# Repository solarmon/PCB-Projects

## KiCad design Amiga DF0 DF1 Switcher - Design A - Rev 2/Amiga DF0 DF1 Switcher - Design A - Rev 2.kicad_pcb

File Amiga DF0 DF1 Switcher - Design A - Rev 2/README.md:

# Amiga DF0 DF1 Switcher - Design A - Rev 2

This is an Amiga A500/A500+ DF0/DF1 Switcher. It has been designed to sit directly on the floppy drive data port, and for the floppy power to connect to it. It then splits them out so that two internal drives can be connected.

It can work in two modes:

* **DF0 / DF1 Switcher** - this switches DF0 and DF1 between the two internal drives. 
* **DF0 Selector** - this switches only DF0 between the two internal drive - so only one drive will be DF0.

This switching / selection is done using a DPDT On-On switch connected to the **SW1** header pins.

The **JP1** jumper connects or disconnects SEL1. This effectively changes the mode without messing about with the DPDT switch:

* **JP1 Bridged** - DF0/DF1 Switcher mode
* **JP1 Unbridged** - DFO Selector mode

Top:

Bottom:

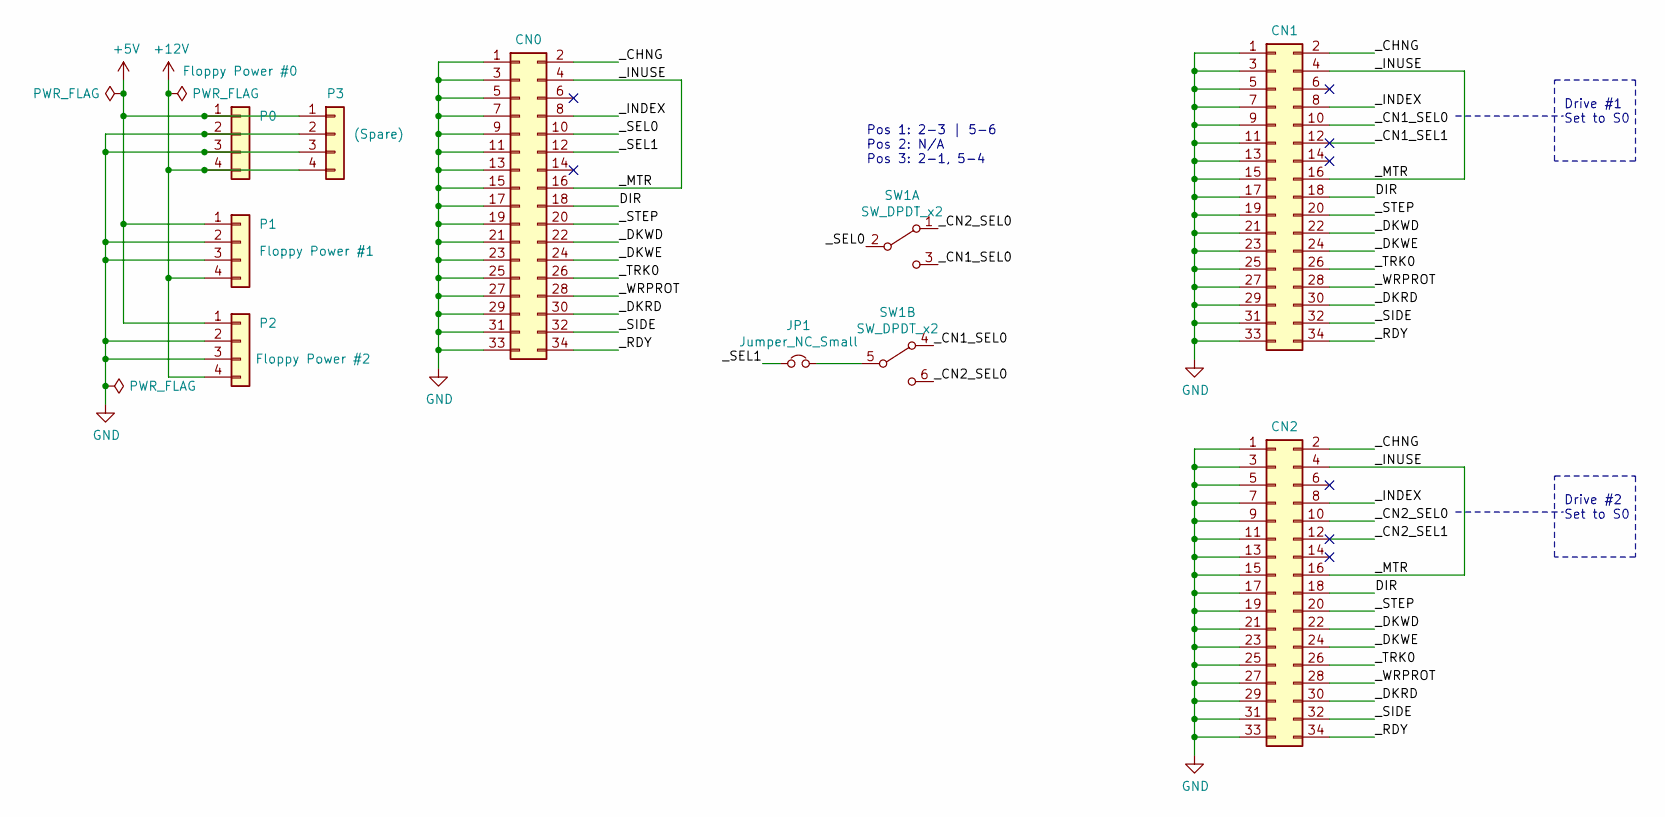
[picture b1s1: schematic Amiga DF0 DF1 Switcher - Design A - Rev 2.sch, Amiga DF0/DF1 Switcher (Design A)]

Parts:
CN0: Conn_02x17_Odd_Even; PinSocket_2x17_P2.54mm_Vertical
CN1, CN2: Conn_02x17_Odd_Even; PinHeader_2x17_P2.54mm_Vertical
JP1: Jumper_NC_Small; PinHeader_1x02_P2.54mm_Vertical
P0: Floppy Power #0; PinHeader_1x04_P2.54mm_Vertical
P1: Floppy Power #1; PinHeader_1x04_P2.54mm_Vertical
P2: Floppy Power #2; PinHeader_1x04_P2.54mm_Vertical
P3: (Spare); PinHeader_1x04_P2.54mm_Vertical
SW1: SW_DPDT_x2; PinHeader_2x03_P2.54mm_Vertical_DPDT

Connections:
+5V: P0.1, P1.1, P2.1, P3.1
+12V: P0.4, P1.4, P2.4, P3.4
/DIR: CN0.18, CN1.18, CN2.18
/_CHNG: CN0.2, CN1.2, CN2.2
/_CN1_SEL0: CN1.10, SW1.3 (C), SW1.4 (A)
/_CN1_SEL1: CN1.12
/_CN2_SEL0: CN2.10, SW1.1 (A), SW1.6 (C)
/_CN2_SEL1: CN2.12
/_DKRD: CN0.30, CN1.30, CN2.30
/_DKWD: CN0.22, CN1.22, CN2.22
/_DKWE: CN0.24, CN1.24, CN2.24
/_INDEX: CN0.8, CN1.8, CN2.8
/_INUSE: CN0.4, CN0.16, CN1.4, CN1.16, CN2.4, CN2.16
/_RDY: CN0.34, CN1.34, CN2.34
/_SEL0: CN0.10, SW1.2 (B)
/_SEL1: CN0.12, JP1.1
/_SIDE: CN0.32, CN1.32, CN2.32
/_STEP: CN0.20, CN1.20, CN2.20
/_TRK0: CN0.26, CN1.26, CN2.26
/_WRPROT: CN0.28, CN1.28, CN2.28
GND: CN0.1, CN0.3, CN0.5, CN0.7, CN0.9, CN0.11, CN0.13, CN0.15, CN0.17, CN0.19, CN0.21, CN0.23, CN0.25, CN0.27, CN0.29, CN0.31, CN0.33, CN1.1, CN1.3, CN1.5, CN1.7, CN1.9, CN1.11, CN1.13, CN1.15, CN1.17, CN1.19, CN1.21, CN1.23, CN1.25, CN1.27, CN1.29, CN1.31, CN1.33, CN2.1, CN2.3, CN2.5, CN2.7, CN2.9, CN2.11, CN2.13, CN2.15, CN2.17, CN2.19, CN2.21, CN2.23, CN2.25, CN2.27, CN2.29, CN2.31, CN2.33, P0.2, P0.3, P1.2, P1.3, P2.2, P2.3, P3.2, P3.3
unnamed: JP1.2, SW1.5 (B)

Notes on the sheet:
Drive #1 Set to S0
Drive #2 Set to S0
Pos 1: 2-3 | 5-6 Pos 2: N/A Pos 3: 2-1, 5-4

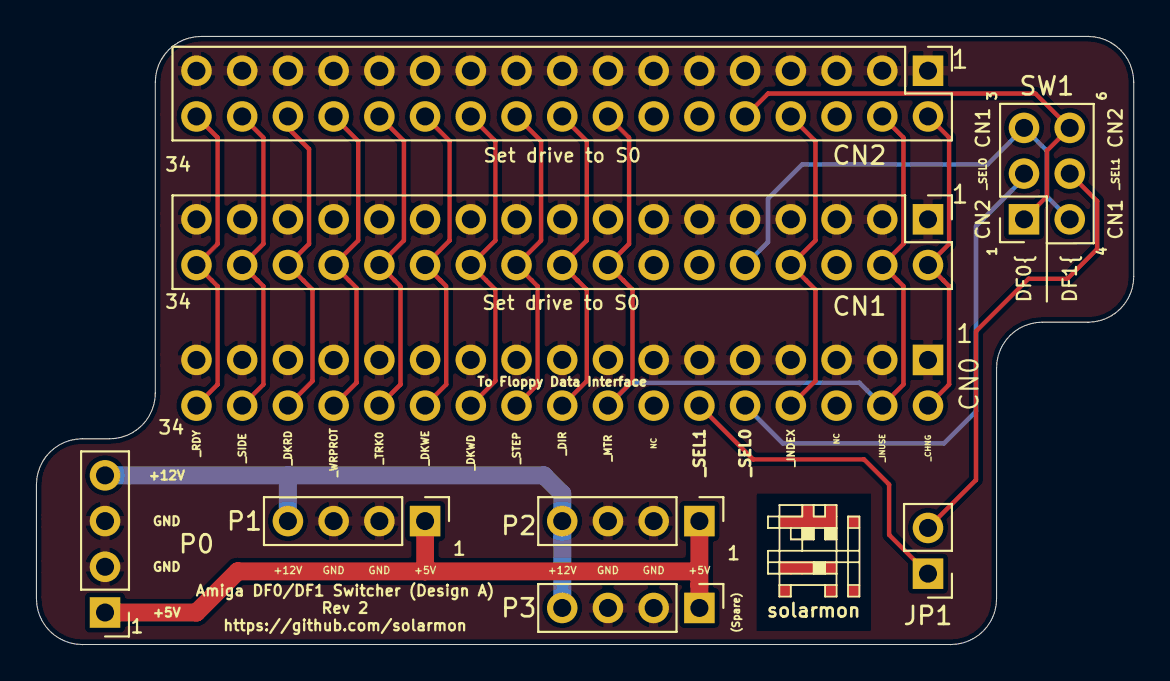
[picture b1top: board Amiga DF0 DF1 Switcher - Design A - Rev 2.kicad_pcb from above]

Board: 2 copper layers, 61.0 x 33.8 mm, 10 parts (1 on the bottom side), 20 nets.

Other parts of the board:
solarmon: solarmon-logo-25mils

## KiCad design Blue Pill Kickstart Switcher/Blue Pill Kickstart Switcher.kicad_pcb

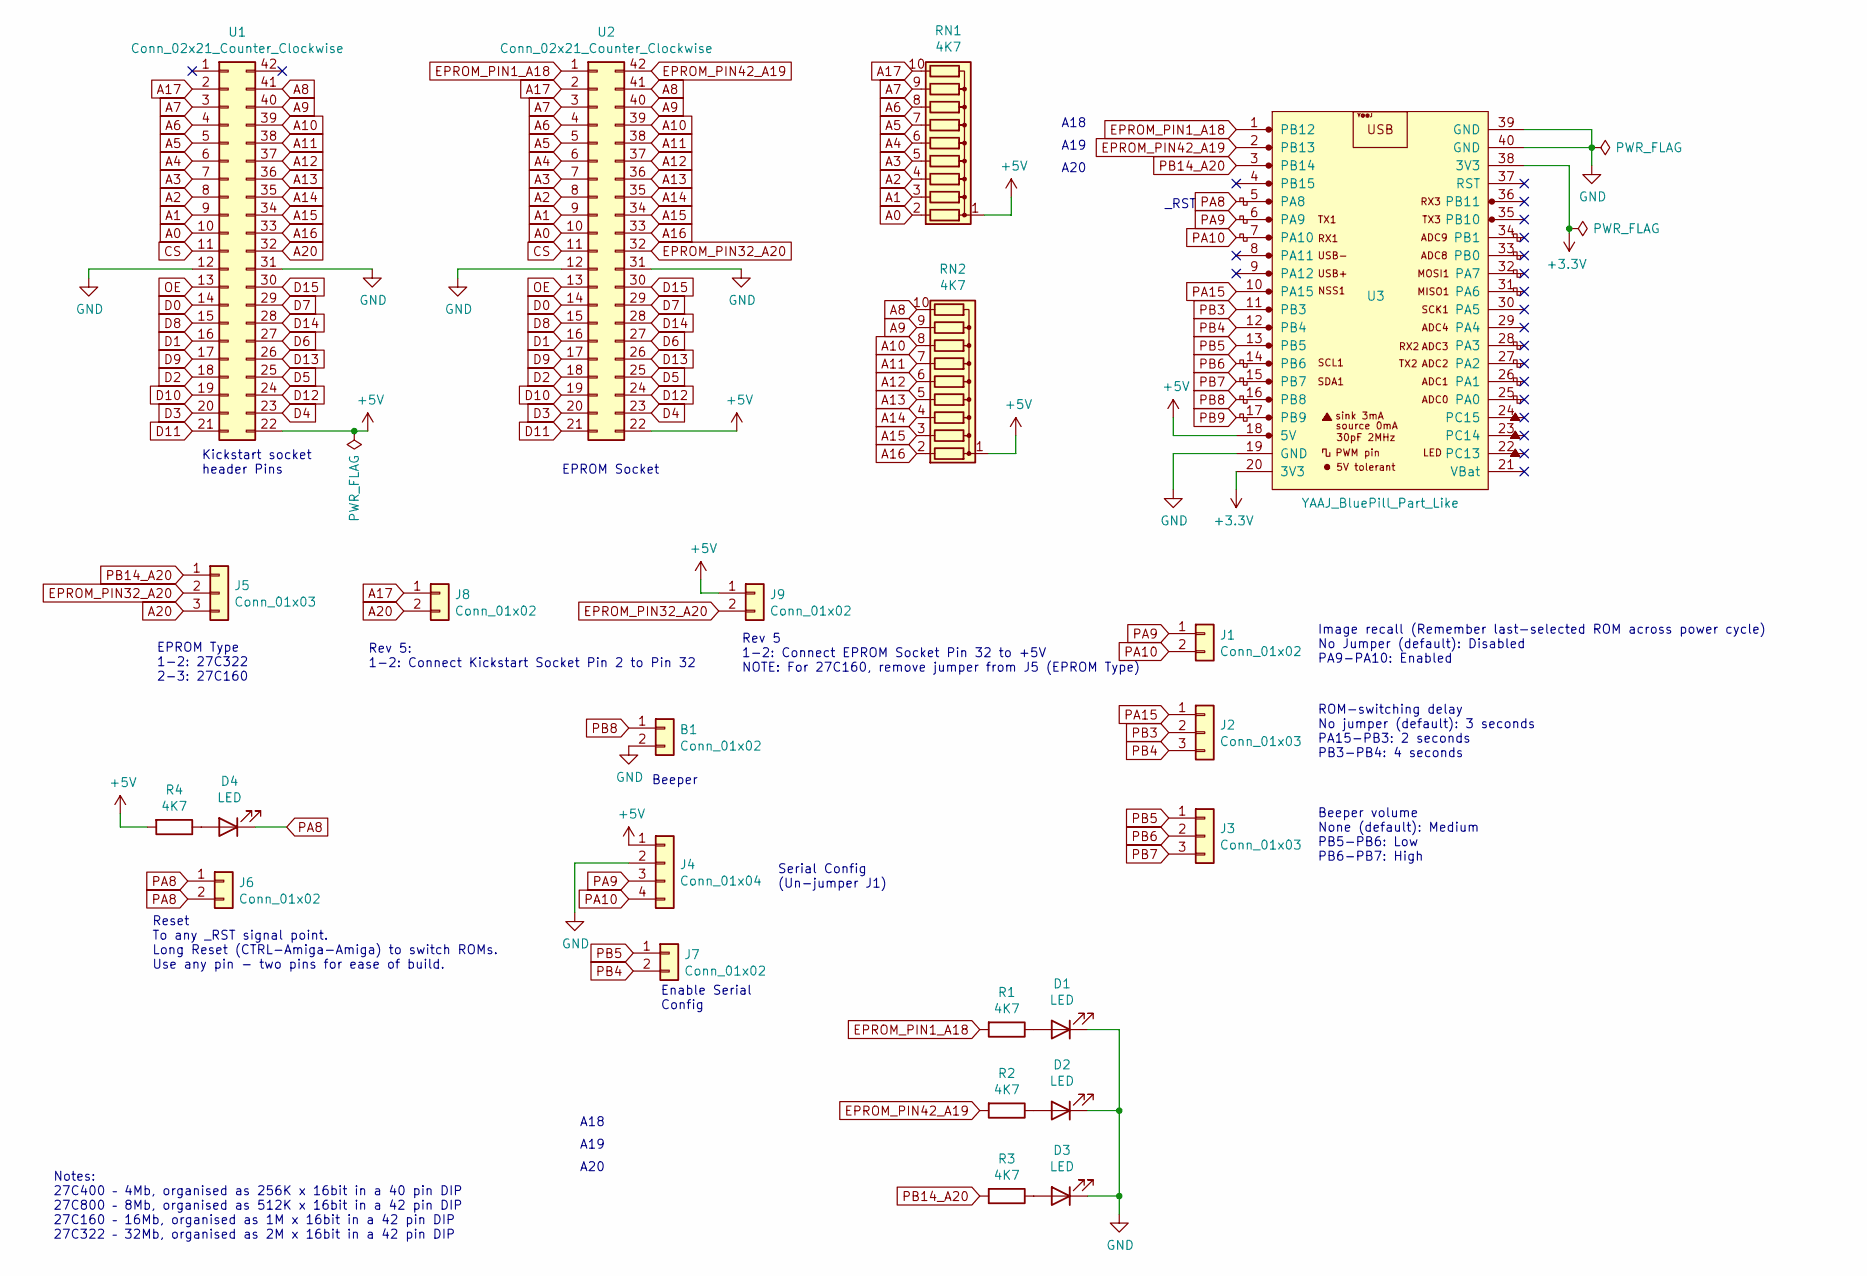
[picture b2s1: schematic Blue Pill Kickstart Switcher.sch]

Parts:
B1: Conn_01x02; Buzzer
D1, D2, D3, D4: LED; LED_0805_2012Metric_Pad1.15x1.40mm_HandSolder
J1, J6, J7, J8, J9: Conn_01x02; PinHeader_1x02_P2.54mm_Horizontal
J2, J3, J5: Conn_01x03; PinHeader_1x03_P2.54mm_Horizontal
J4: Conn_01x04; PinHeader_1x04_P2.54mm_Horizontal
R1, R2, R3, R4: 4K7; R_0805_2012Metric_Pad1.20x1.40mm_HandSolder
RN1, RN2: 4K7; R_Array_SIP10
U1: Conn_02x21_Counter_Clockwise; DIP-42_W15.24mm_Pin_Header_Bottom
U2: Conn_02x21_Counter_Clockwise; DIP-42_W15.24mm_Socket
U3: YAAJ_BluePill_Part_Like; YAAJ_BluePill_1

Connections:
+3V3: U3.20 (3V3), U3.38 (3V3)
+5V: J4.1, J9.1, R4.2, RN1.1 (common), RN2.1 (common), U1.22, U2.22, U3.18 (5V)
A0: RN1.2 (R1), U1.10, U2.10
A1: RN1.3 (R2), U1.9, U2.9
A2: RN1.4 (R3), U1.8, U2.8
A3: RN1.5 (R4), U1.7, U2.7
A4: RN1.6 (R5), U1.6, U2.6
A5: RN1.7 (R6), U1.5, U2.5
A6: RN1.8 (R7), U1.4, U2.4
A7: RN1.9 (R8), U1.3, U2.3
A8: RN2.10 (R9), U1.41, U2.41
A9: RN2.9 (R8), U1.40, U2.40
A10: RN2.8 (R7), U1.39, U2.39
A11: RN2.7 (R6), U1.38, U2.38
A12: RN2.6 (R5), U1.37, U2.37
A13: RN2.5 (R4), U1.36, U2.36
A14: RN2.4 (R3), U1.35, U2.35
A15: RN2.3 (R2), U1.34, U2.34
A16: RN2.2 (R1), U1.33, U2.33
A17: J8.1, RN1.10 (R9), U1.2, U2.2
A20: J5.3, J8.2, U1.32
CS: U1.11, U2.11
D0: U1.14, U2.14
D1: U1.16, U2.16
D2: U1.18, U2.18
D3: U1.20, U2.20
D4: U1.23, U2.23
D5: U1.25, U2.25
D6: U1.27, U2.27
D7: U1.29, U2.29
D8: U1.15, U2.15
D9: U1.17, U2.17
D10: U1.19, U2.19
D11: U1.21, U2.21
D12: U1.24, U2.24
D13: U1.26, U2.26
D14: U1.28, U2.28
D15: U1.30, U2.30
EPROM_PIN1_A18: R1.2, U2.1, U3.1 (PB12)
EPROM_PIN32_A20: J5.2, J9.2, U2.32
EPROM_PIN42_A19: R2.2, U2.42, U3.2 (PB13)
GND: B1.2, D1.1 (K), D2.1 (K), D3.1 (K), J4.2, U1.12, U1.31, U2.12, U2.31, U3.19 (GND), U3.39 (GND), U3.40 (GND)
unnamed: D1.2 (A), R1.1
unnamed: D2.2 (A), R2.1
unnamed: D3.2 (A), R3.1
unnamed: D4.2 (A), R4.1
OE: U1.13, U2.13
PA8: D4.1 (K), J6.1, J6.2, U3.5 (PA8)
PA9: J1.1, J4.3, U3.6 (PA9)
PA10: J1.2, J4.4, U3.7 (PA10)
PA15: J2.1, U3.10 (PA15)
PB3: J2.2, U3.11 (PB3)
PB4: J2.3, J7.2, U3.12 (PB4)
PB5: J3.1, J7.1, U3.13 (PB5)
PB6: J3.2, U3.14 (PB6)
PB7: J3.3, U3.15 (PB7)
PB8: B1.1, U3.16 (PB8)
PB9: U3.17 (PB9)
PB14_A20: J5.1, R3.2, U3.3 (PB14)

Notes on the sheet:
Beeper
Beeper volume None (default): Medium PB5-PB6: Low PB6-PB7: High
Image recall (Remember last-selected ROM across power cycle) No Jumper (default): Disabled PA9-PA10: Enabled
ROM-switching delay No jumper (default): 3 seconds PA15-PB3: 2 seconds PB3-PB4: 4 seconds
Serial Config (Un-jumper J1)
Enable Serial Config
Notes: 27C400 – 4Mb, organised as 256K x 16bit in a 40 pin DIP 27C800 – 8Mb, organised as 512K x 16bit in a 42 pin DIP 27C160 – 16Mb, organised as 1M x 16bit in a 42 pin DIP 27C322 – 32Mb, organised as 2M x 16bit in a 42 pin DIP
_RST
EPROM Socket
Kickstart socket header Pins
A18
A19
A20
Reset To any _RST signal point. Long Reset (CTRL-Amiga-Amiga) to switch ROMs. Use any pin - two pins for ease of build.
EPROM Type 1-2: 27C322 2-3: 27C160
Rev 5: 1-2: Connect Kickstart Socket Pin 2 to Pin 32
Rev 5 1-2: Connect EPROM Socket Pin 32 to +5V NOTE: For 27C160, remove jumper from J5 (EPROM Type)

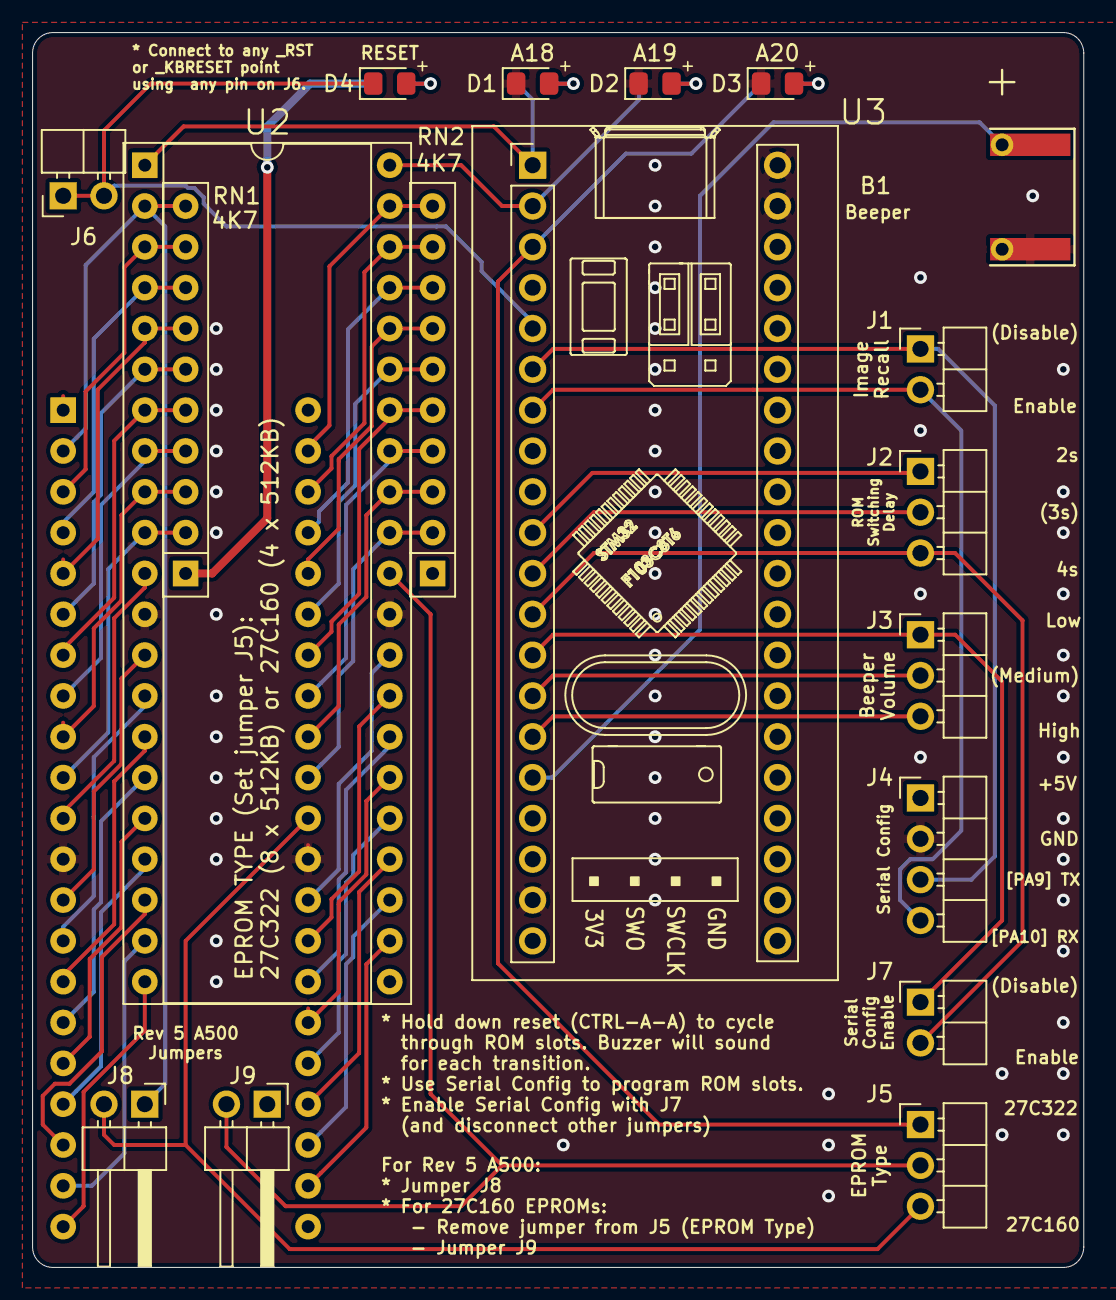
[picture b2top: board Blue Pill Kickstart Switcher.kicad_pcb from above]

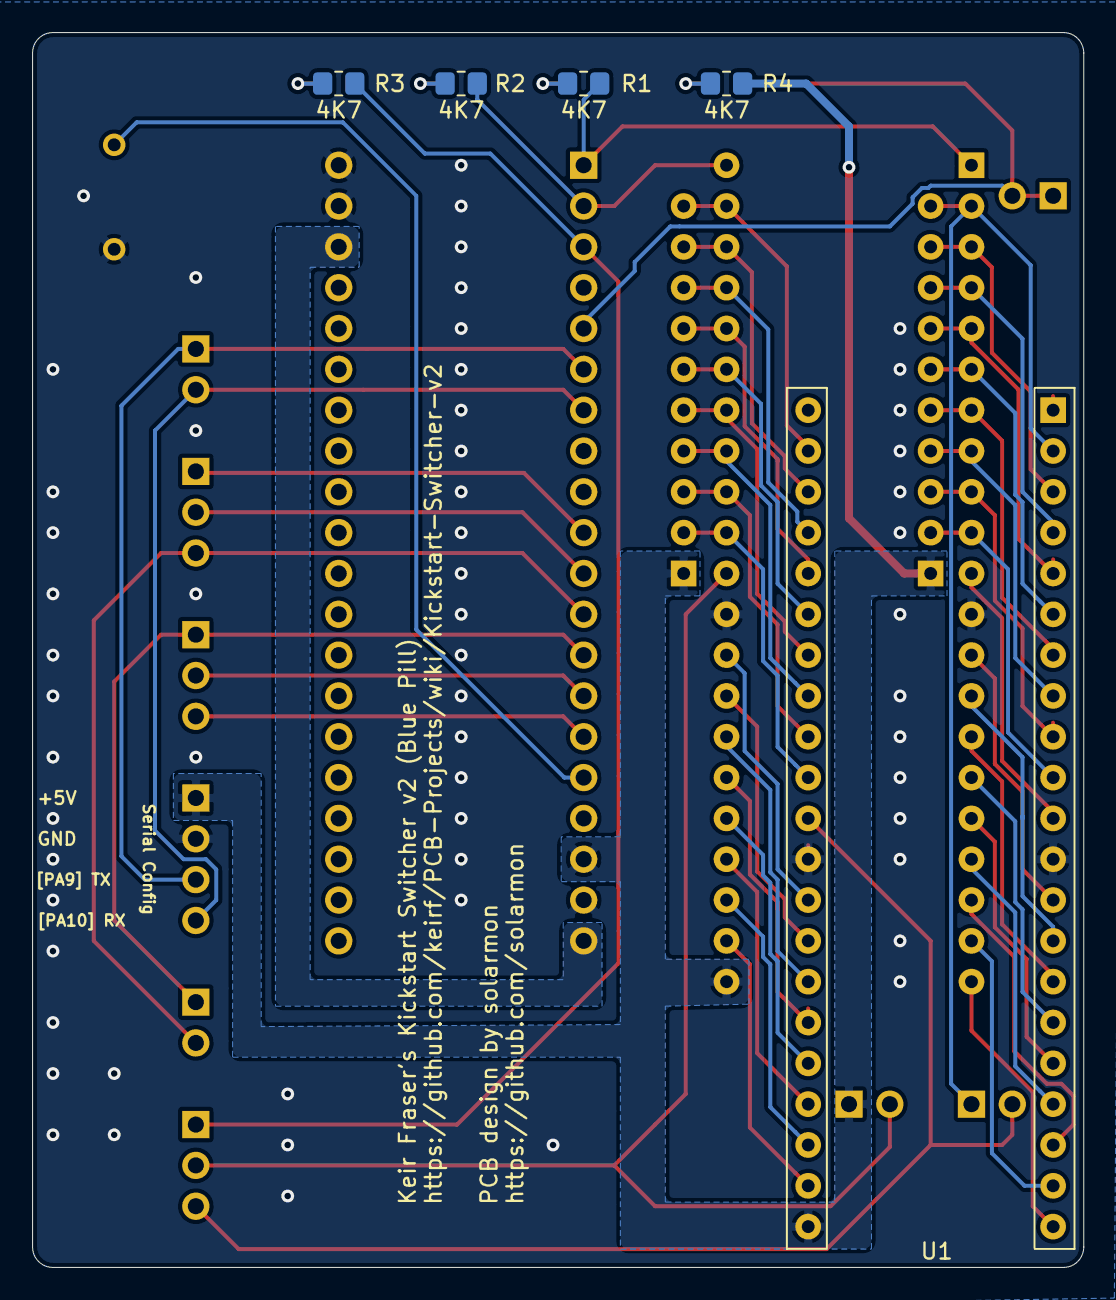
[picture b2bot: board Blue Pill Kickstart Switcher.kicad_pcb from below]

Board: 2 copper layers, 65.4 x 76.8 mm, 23 parts (4 on the bottom side), 58 nets.

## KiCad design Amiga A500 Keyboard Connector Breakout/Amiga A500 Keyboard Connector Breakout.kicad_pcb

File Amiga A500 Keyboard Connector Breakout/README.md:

# Amiga A500 Keyboard Connector Breakout

This is a breakout board for the A500/A500+ keyboard connector to allow access to the signals on it.

The keyboard connector has the following pinouts and signals:

1. _KBCLOCK
2. _KBDATA
3. _KBRESET
4. +5V
5. (KEY)
6. GND
7. STATUS (POWER LED)
8. INUSE (DRIVE LED)

The board provides a female header at the bottom of the board that sits on the keyboard connector on the motherboard, and provides two sets of corresponding header pins - one for the keyboard plug to connect to and the other for as per user requirements.

The board also has an LED for the the _KBRESET, STATUS and INUSE signals to provide a quick indicate of the state of those signals. This also means you don't need a keyboard connected to see the POWER and DRIVE LEDs.

The board also provides some pin headers for the +5V and GND power rails, useful to power additional boards and for diagnostics tools such as a logic probe.

Top of the breakout board:

Bottom of the breakout board:

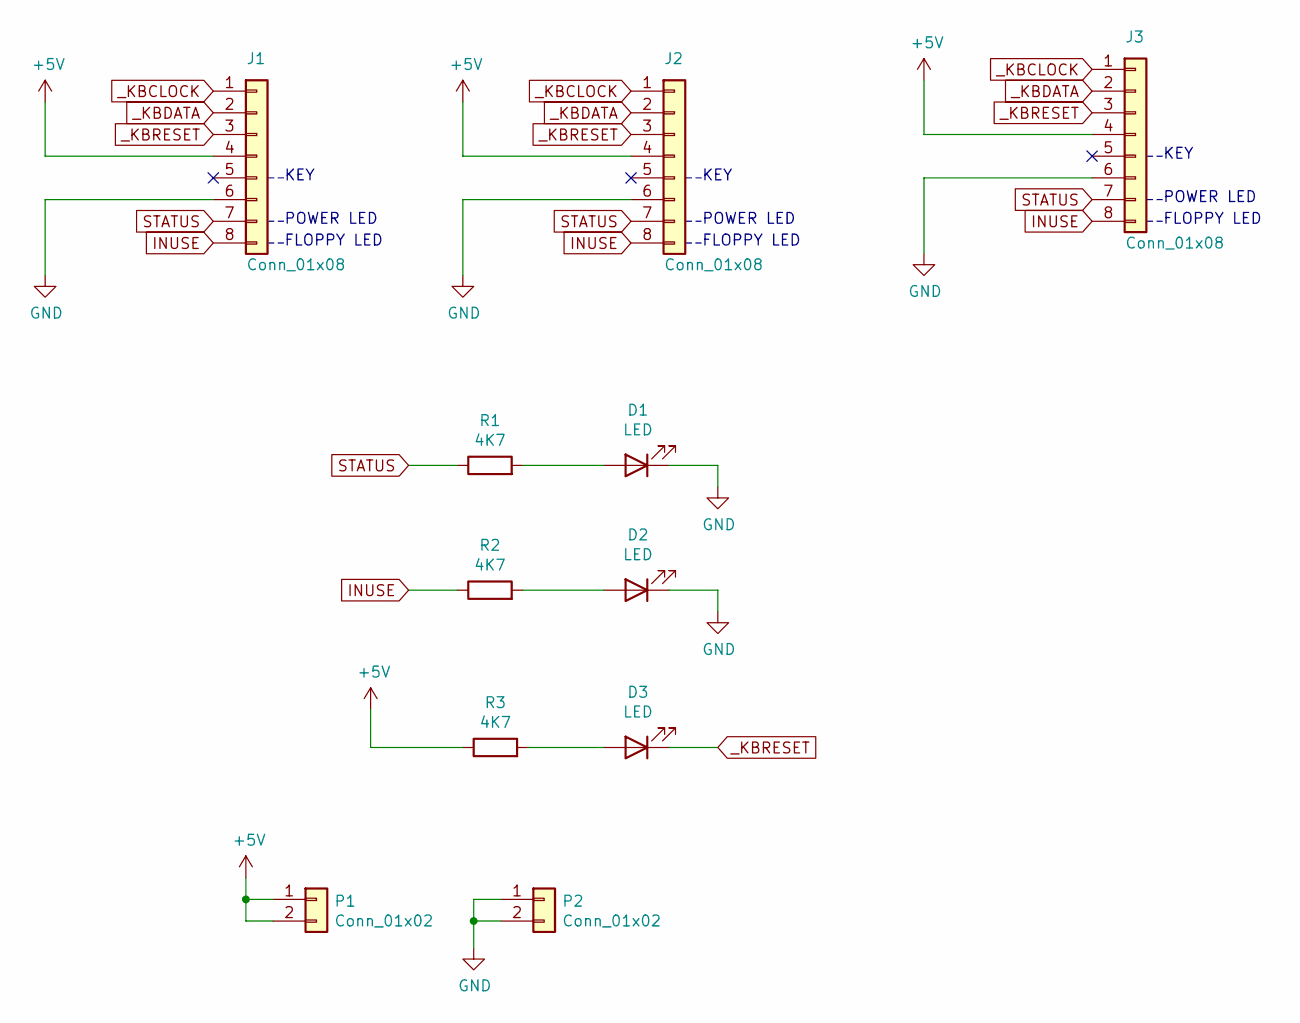
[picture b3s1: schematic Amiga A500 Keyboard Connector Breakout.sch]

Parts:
D1, D2, D3: LED; LED_0805_2012Metric_Pad1.15x1.40mm_HandSolder
J1: Conn_01x08; PinSocket_1x08_P2.54mm_Vertical
J2, J3: Conn_01x08; PinHeader_1x08_P2.54mm_Vertical
P1, P2: Conn_01x02; PinHeader_1x02_P2.54mm_Vertical
R1, R2, R3: 4K7; R_0805_2012Metric_Pad1.20x1.40mm_HandSolder

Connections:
+5V: J1.4, J2.4, J3.4, P1.1, P1.2, R3.1
GND: D1.1 (K), D2.1 (K), J1.6, J2.6, J3.6, P2.1, P2.2
INUSE: J1.8, J2.8, J3.8, R2.1
unnamed: D1.2 (A), R1.2
unnamed: D2.2 (A), R2.2
unnamed: D3.2 (A), R3.2
STATUS: J1.7, J2.7, J3.7, R1.1
_KBCLOCK: J1.1, J2.1, J3.1
_KBDATA: J1.2, J2.2, J3.2
_KBRESET: D3.1 (K), J1.3, J2.3, J3.3

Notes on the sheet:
POWER LED
FLOPPY LED
KEY

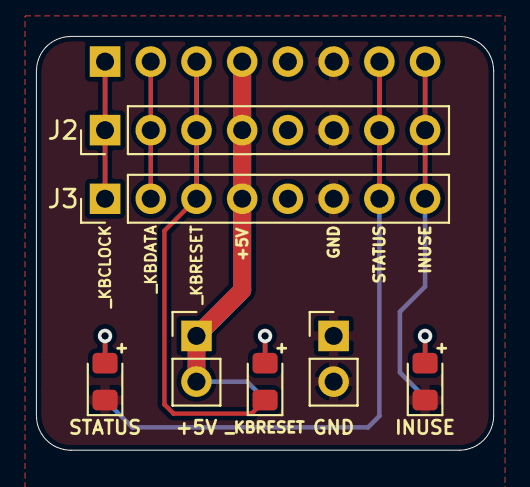
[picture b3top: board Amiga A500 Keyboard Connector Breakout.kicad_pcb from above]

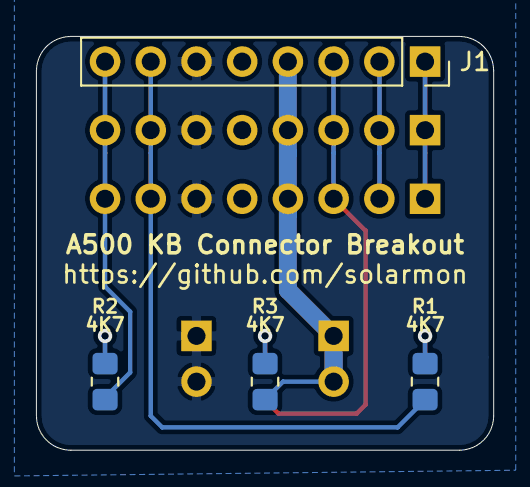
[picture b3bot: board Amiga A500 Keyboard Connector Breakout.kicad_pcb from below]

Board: 2 copper layers, 25.4 x 23.0 mm, 11 parts (4 on the bottom side), 10 nets.

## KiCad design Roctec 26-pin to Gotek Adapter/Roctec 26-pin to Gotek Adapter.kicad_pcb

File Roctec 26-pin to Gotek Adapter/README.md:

# Roctec 26-pin to Gotek Adapter

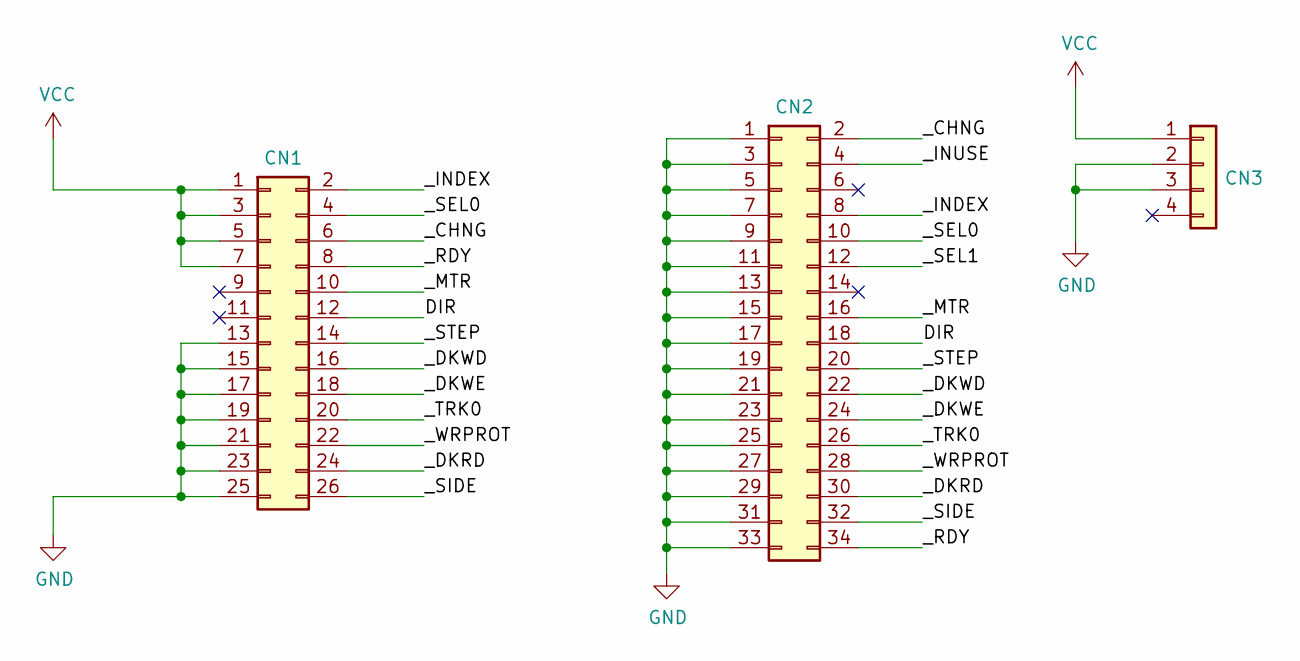
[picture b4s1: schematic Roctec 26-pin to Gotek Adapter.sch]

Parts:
CN1: Conn_02x13_Odd_Even; PinHeader_2x13_P2.54mm_Vertical
CN2: Conn_02x17_Odd_Even; PinSocket_1x17_P2.54mm_Horizontal
CN3: Conn_01x04; PinSocket_1x04_P2.54mm_Horizontal

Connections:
/DIR: CN1.12, CN2.18
/_CHNG: CN1.6, CN2.2
/_DKRD: CN1.24, CN2.30
/_DKWD: CN1.16, CN2.22
/_DKWE: CN1.18, CN2.24
/_INDEX: CN1.2, CN2.8
/_INUSE: CN2.4
/_MTR: CN1.10, CN2.16
/_RDY: CN1.8, CN2.34
/_SEL0: CN1.4, CN2.10
/_SEL1: CN2.12
/_SIDE: CN1.26, CN2.32
/_STEP: CN1.14, CN2.20
/_TRK0: CN1.20, CN2.26
/_WRPROT: CN1.22, CN2.28
GND: CN1.13, CN1.15, CN1.17, CN1.19, CN1.21, CN1.23, CN1.25, CN2.1, CN2.3, CN2.5, CN2.7, CN2.9, CN2.11, CN2.13, CN2.15, CN2.17, CN2.19, CN2.21, CN2.23, CN2.25, CN2.27, CN2.29, CN2.31, CN2.33, CN3.2, CN3.3
VCC: CN1.1, CN1.3, CN1.5, CN1.7, CN3.1

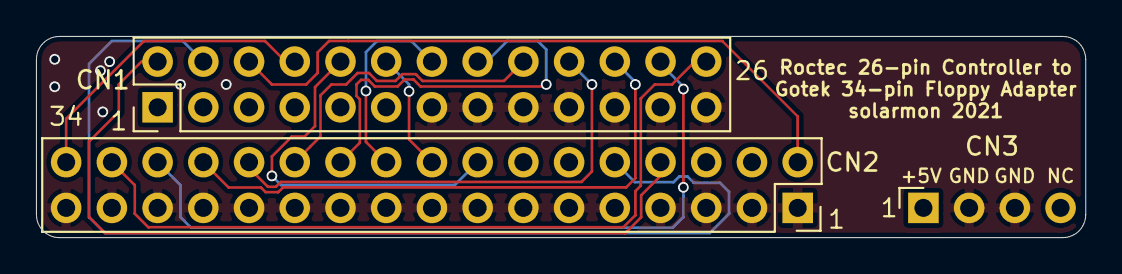
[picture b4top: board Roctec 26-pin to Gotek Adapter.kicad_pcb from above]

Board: 2 copper layers, 58.3 x 11.2 mm, 3 parts (0 on the bottom side), 15 nets.

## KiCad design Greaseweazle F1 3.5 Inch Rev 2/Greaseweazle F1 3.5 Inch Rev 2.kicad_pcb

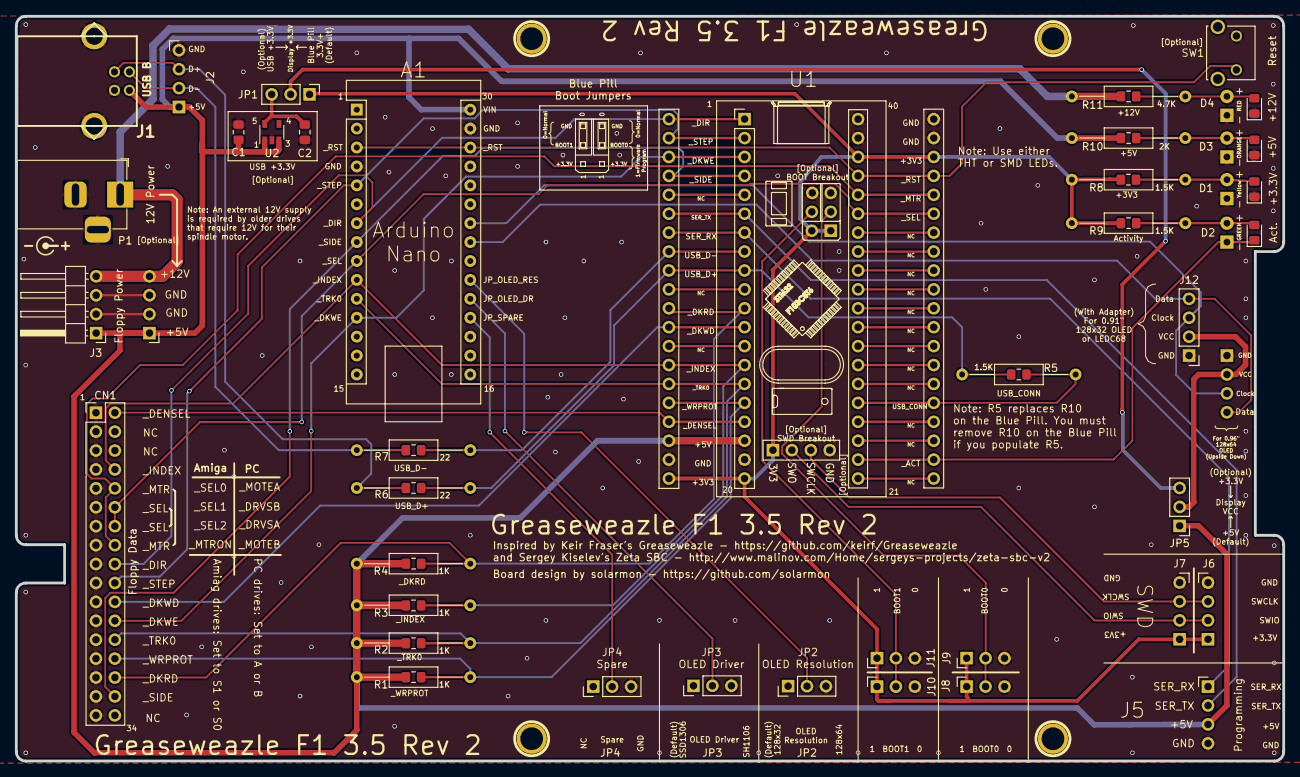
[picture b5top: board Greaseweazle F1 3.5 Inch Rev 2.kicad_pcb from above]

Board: 2 copper layers, 170.2 x 100.0 mm, 67 parts (1 on the bottom side), 56 nets.

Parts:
A1: Arduino_Nano_v3.x; Arduino_Nano
BP1, BP2: Conn_01x20_Male; PinHeader_1x20_P2.54mm_Vertical
C1, C2: 1u; C_0805_2012Metric_Pad1.15x1.40mm_HandSolder
CN1: Floppy Data; PinHeader_2x17_P2.54mm_Vertical
D1: +3V3 LED; LED_0805_2012Metric_Pad1.15x1.40mm_HandSolder
D1#2, D2#2, D3#2, D4: LED_D3.0mm_Horizontal_O1.27mm_Z6.0mm
D2: ACT LED; LED_0805_2012Metric_Pad1.15x1.40mm_HandSolder
D3, D4#2: +5V LED; LED_0805_2012Metric_Pad1.15x1.40mm_HandSolder
Floppy Drive: Floppy_Drive
HEX: Hex_standoff_m3_15mm
HEX#2, HEX#3, HEX#4: Hex_standoff_m3_15mm
HOLE1, HOLE2, HOLE3, HOLE4: CONN_1; HOLE_3MM
J1: USB B; conn_usb_B
J2: USB Header; PinHeader_1x04_P2.54mm_Horizontal
J3: Floppy Power; PinHeader_1x04_P2.54mm_Horizontal
J4: Floppy Power Header; PinHeader_1x04_P2.54mm_Horizontal
J5: Programming Port; PinHeader_1x04_P2.54mm_Horizontal
J6, J7: SWD Port; PinHeader_1x04_P2.54mm_Horizontal
J8, J9, J10, J11: Conn_01x03; PinHeader_1x03_P2.54mm_Horizontal
J12, J13: Display Port; PinHeader_1x04_P2.54mm_Vertical
JP1, JP2, JP3, JP4, JP5: Jumper_3_Bridged12; PinHeader_1x03_P2.54mm_Vertical
P1: 12V Power; BarrelJack_Horizontal
R1, R2, R3, R4: 1K; R_0805_2012Metric_Pad1.15x1.40mm_HandSolder
R1#2, R2#2, R3#2, R4#2, R5#2, R6#2, R7#2, R8#2, R9#2, R10#2, R11: R_Axial_DIN0207_L6.3mm_D2.5mm_P15.24mm_Horizontal
R5, R8, R9: 1.5K; R_0805_2012Metric_Pad1.15x1.40mm_HandSolder
R6, R7: 22; R_0805_2012Metric_Pad1.15x1.40mm_HandSolder
R10: 2K; R_0805_2012Metric_Pad1.15x1.40mm_HandSolder
R11#2: 4.7K; R_0805_2012Metric_Pad1.15x1.40mm_HandSolder
SW1: Reset; PUSH_BUTTON_RIGHT_ANGLE
U1: Blue Pill; YAAJ_BluePill_SWD_1_BootPins
U2: AP2112K-3.3; SOT-23-5

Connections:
+3V3: BP1.20, BP2.18, J6.1, J7.1, J8.1, J9.1, J10.1, J11.1, JP1.1, R8.2, R8#2.2, R9.2, R9#2.2, U1.20, U1.38, U1.41, U1.45, U1.48
+5V: A1.30, BP1.18, C1.1, J1.1, J2.1, J3.1, J4.1, J5.3, JP5.1, R1.1, R1#2.2, R2.1, R2#2.2, R3.1, R3#2.2, R4.1, R4#2.2, R10.2, R10#2.2, U1.18, U2.1, U2.3
+12V: J3.4, J4.4, P1.1, R11.2, R11#2.2
/BOOT0: J8.2, J9.2, U1.46
/BOOT1: J10.2, J11.2, U1.49
/Display_3V3: JP1.2, JP5.3
/Display_Clock: A1.24, J12.3, J13.3
/Display_Data: A1.23, J12.4, J13.4
/Display_VCC: J12.2, J13.2, JP5.2
/JP_OLED_DR: A1.20, JP3.2
/JP_OLED_RES: A1.21, JP2.2
/JP_SPARE: A1.19, JP4.2
/SER_RX: BP1.7, J5.1, U1.7
/SER_TX: BP1.6, J5.2, U1.6
/SWD_SWCLK: J6.3, J7.3, U1.43
/SWD_SWIO: J6.2, J7.2, U1.42
/USB_3V3: C2.1, JP1.3, U2.5
/USB_CONN: BP2.5, R5.2, R5#2.2, U1.25
/USB_D+: BP1.9, R5.1, R5#2.1, R6.2, R6#2.1, U1.9
/USB_D-: BP1.8, R7.2, R7#2.1, U1.8
/_ACT: BP2.2, D2.1, D2#2.1, U1.22
/_DENSEL: BP1.17, CN1.2, U1.17
/_DIR: A1.7, BP1.1, CN1.18, U1.1
/_DKRD: BP1.11, CN1.30, R4.2, R4#2.1, U1.11
/_DKWD: BP1.12, CN1.22, U1.12
/_DKWE: A1.12, BP1.3, CN1.24, U1.3
/_INDEX: A1.10, BP1.14, CN1.8, R3.2, R3#2.1, U1.14
/_MTR: BP2.16, CN1.10, CN1.16, U1.36
/_RST: A1.3, A1.28, BP2.17, SW1.1, U1.37
/_SEL: A1.9, BP2.15, CN1.12, CN1.14, U1.35
/_SIDE: A1.8, BP1.4, CN1.32, U1.4
/_STEP: A1.5, BP1.2, CN1.20, U1.2
/_TRK0: A1.11, BP1.15, CN1.26, R2.2, R2#2.1, U1.15
/_WRPROT: BP1.16, CN1.28, R1.2, R1#2.1, U1.16
GND: A1.4, A1.29, BP1.19, BP2.19, BP2.20, C1.2, C2.2, CN1.1, CN1.3, CN1.5, CN1.7, CN1.9, CN1.11, CN1.13, CN1.15, CN1.17, CN1.19, CN1.21, CN1.23, CN1.25, CN1.27, CN1.29, CN1.31, CN1.33, D1.1, D1#2.1, D3.1, D3#2.1, D4.1, D4#2.1, HOLE1.1, HOLE2.1, HOLE3.1, HOLE4.1, J1.4, J1.5, J2.4, J3.2, J3.3, J4.2, J4.3, J5.4, J6.4, J7.4, J8.3, J9.3, J10.3, J11.3, J12.1, J13.1, JP2.3, JP3.3, JP4.3, P1.2, P1.3, SW1.2, U1.19, U1.39, U1.40, U1.44, U1.47, U1.50, U2.2
unnamed: BP1.5, U1.5
unnamed: BP1.10, U1.10
unnamed: BP1.13, U1.13
unnamed: BP2.1, U1.21
unnamed: BP2.3, U1.23
unnamed: BP2.4, U1.24
unnamed: BP2.6, U1.26
unnamed: BP2.7, U1.27
unnamed: BP2.8, U1.28
unnamed: BP2.9, U1.29
unnamed: BP2.10, U1.30
unnamed: BP2.11, U1.31
unnamed: BP2.12, U1.32
unnamed: BP2.13, U1.33
unnamed: BP2.14, U1.34
unnamed: D1.2, D1#2.2, R8.1, R8#2.1
unnamed: D2.2, D2#2.2, R9.1, R9#2.1
unnamed: D3.2, D3#2.2, R10.1, R10#2.1
unnamed: D4.2, D4#2.2, R11.1, R11#2.1
unnamed: J1.2, J2.2, R7.1, R7#2.2
unnamed: J1.3, J2.3, R6.1, R6#2.2

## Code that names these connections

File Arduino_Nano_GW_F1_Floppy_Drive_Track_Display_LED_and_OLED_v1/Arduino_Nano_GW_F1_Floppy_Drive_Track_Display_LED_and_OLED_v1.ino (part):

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const byte STEP_Pin = 2;   // D2 (D2 and D3 are interrupt capable)

int DIR_Pin = 4;    // D4
int SIDE_Pin = 5;   // D5
int SEL_Pin = 6;   // D6
int INDEX_Pin = 7;  // D7
int TRK0_Pin = 8;   // D8
int DKWE_Pin = 9;   // D9

int JP_SPARE_Pin = 14;      // D14 / A0
int JP_OLED_DR_Pin = 15;    // D15 / A1
int JP_OLED_RES_Pin = 16;   // D16 / A2


// variables to store the drive signal states
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  // Make interrupt for STEP pin, so that falling edge can be detected.
  pinMode(STEP_Pin, INPUT_PULLUP);
  attachInterrupt(digitalPinToInterrupt(STEP_Pin), stepping, FALLING);
  pinMode(INDEX_Pin, INPUT_PULLUP);
  pinMode(SIDE_Pin, INPUT_PULLUP);
  pinMode(TRK0_Pin, INPUT_PULLUP);
  pinMode(SEL_Pin, INPUT_PULLUP);
  pinMode(DKWE_Pin, INPUT_PULLUP);

  //----------------------------

  // Check Jumpers

  pinMode(JP_SPARE_Pin, INPUT_PULLUP);
  pinMode(JP_OLED_RES_Pin, INPUT_PULLUP);
  pinMode(JP_OLED_DR_Pin, INPUT_PULLUP);

  JP_SPARE_State = digitalRead(JP_SPARE_Pin);
  JP_OLED_RES_State = digitalRead(JP_OLED_RES_Pin);
  JP_OLED_DR_State = digitalRead(JP_OLED_DR_Pin);

  Serial.print(F("### JP_SPARE_State: "));
  Serial.print(JP_SPARE_State);
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          // Poll the drive signals
          DIR_State = digitalRead(DIR_Pin);
          STEP_State = digitalRead(STEP_Pin);
          SIDE_State = digitalRead(SIDE_Pin);
          INDEX_State = digitalRead(INDEX_Pin);
          TRK0_State = digitalRead(TRK0_Pin);
          SEL_State = digitalRead(SEL_Pin); // LOW = STEP IN; HIGH = STEP OUT
          DKWE_State = digitalRead(DKWE_Pin);

          if (TRK0_State == 0)
          {
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
          DIR_State = digitalRead(DIR_Pin);
          STEP_State = digitalRead(STEP_Pin);
          SIDE_State = digitalRead(SIDE_Pin);
          INDEX_State = digitalRead(INDEX_Pin);
          TRK0_State = digitalRead(TRK0_Pin);
          SEL_State = digitalRead(SEL_Pin); // LOW = STEP IN; HIGH = STEP OUT
          DKWE_State = digitalRead(DKWE_Pin);
          
          oled_display.clearDisplay (); // clear display

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
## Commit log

2020-11-21 First draft
2020-11-21 Some improvements
    Made bottom side a filled zone for GND and moved floppy power connector to other side for shorter VCC tracks.
2020-11-21 3D view of board
2020-11-22 More improvements
    * Improved GND net points
    * Test points in appropropriate nets
    * Added additional VCC trace
2020-11-22 Added VCC zone
2020-11-22 More improvements
    * Changed _INDEX signal so that it does not go through a test point.
    * Top row of test points on CN1 now have been put in the appropriate nets
2020-11-22 Created Gerber files
2020-11-22 Tweaked dimensions
    Tweaked dimensions to 70mmx40mm
2020-11-22 Update fp-info-cache
2020-11-24 Added Greaseweazle F1 Gotek (USB-A) project
2020-11-25 Added internal USB header
2020-11-25 Corrected Blue Pill Boot Jumper info
2020-11-25 Added through hole resistor footprints
2020-11-26 Added features
    * Added Activity LED
    * Added resistor pack
    * Added Blue Pill footprint
2020-11-27 More improvements and corrections
    * moved USB header
    * Reset switch
    * Corrected SWD labelling
    * Added DPDT On-On-On toggle switch silk screen
    * Cleaned up LED silk screen
2020-11-27 Added 3D models of Blue Pill and USB A and made some silk screen corrections
2020-11-29 Tweaks and gerber files
2020-12-05 Tweaks
2020-12-08 Tweaks after first build test
    * Increased size of silk screen text
    * Moved notch down a bit
    * Swap +5V and GND on Programming port
    * Moved LED holes nearer towards front.
2020-12-08 Generated gerber files for new build
2020-12-08 Created zipped gerbers
2020-12-20 Added Amiga 34-pin to Citizen Slim 26-pin Adapter - A and B versions
2020-12-20 Greaseweazle F1 in a Gotek Case (USB-A) - latest update
2020-12-20 Added Greaseweazle F1 in a Gotek Case (+ USB B)
2020-12-20 Renamed '26-pin to 34-pin Amiga Floppy Adapter'
    Renamed '26-pin to 34-pin Amiga Floppy Adapter' to 'Roctec 26-pin to Amiga 34-pin Adapter'
2020-12-20 tweak
2020-12-20 Added 'Greaseweazle F1 3.5 Inch'
2020-12-20 Added 12V LED
2020-12-20 Shifted floppy power, and corrected some USB B port traces
2020-12-28 Greaseweazle F1 Gotek Rev 2
    Added "Greaseweazle F1 Gotek Rev 2"
2020-12-30 Latest updates to GW F1 Gotek Rev 2 and GW F1 3.5 rev 2
2020-12-31 Corrected 12V LED resistor from 2K to 4.7K
2021-01-10 Added DWGS.User layer
2021-01-16 Corrected BOOT0 and BOOT0 labels
2021-01-16 Added LEDC68 and 0.9 Inch OLED Adapter project
2021-01-17 Added warning about PCB thickness, and grounded USB shield
2021-01-17 Improved Arduino Nano silk screen details
2021-01-17 Grounded USB shiled, and improved Arduino Nano silkscreen
2021-01-17 Moved J13 for 0.96 inch OLED further forward
2021-01-17 Added Aduino sketch for floppy drive tracker
2021-01-17 Corrected Arduino Nano 3D model orientation
2021-01-17 Added Bumpon 3D model
2021-01-18 Added correctly scaled floppy disk 3d object
2021-01-26 Added missing pin 1 and 34 silkscreen for floppy data connector
2021-03-28 Added GW F1 Gotek and 3.5 rev 2B
2021-03-28 Added Amiga DF0 DF1 Switcher
2021-03-28 Updated gerbers
2021-03-28 Added Greaseweazle logo footprint
2021-04-10 Moved Greaseweazle projects
    Moved Greaseweazle projects to https://github.com/solarmon/Greaseweazl
2021-04-21 Added unused pins to Denise symbol
2021-04-21 Added some dimensions
2021-04-24 Added smaller solarmon logo
2021-04-29 Added Roctec 26-pin to Gotek Adapter
2021-05-15 Added FFC connectors
2021-05-15 Added "Amiga A500 Keyboard Connector Breakout" project
2021-05-15 Added PNG and PDF files
2021-05-15 Added PNG and PDF
2021-05-24 Added "Blue Pill Kickstart Switcher" project
2021-08-15 Added 3D pictures
2021-09-04 Show resistor values in silk screen
2021-09-22 Added Rev 2 of DF0/DF! switchers
2021-09-22 Rev 2 images
2021-09-22 Updated to Rev 2
